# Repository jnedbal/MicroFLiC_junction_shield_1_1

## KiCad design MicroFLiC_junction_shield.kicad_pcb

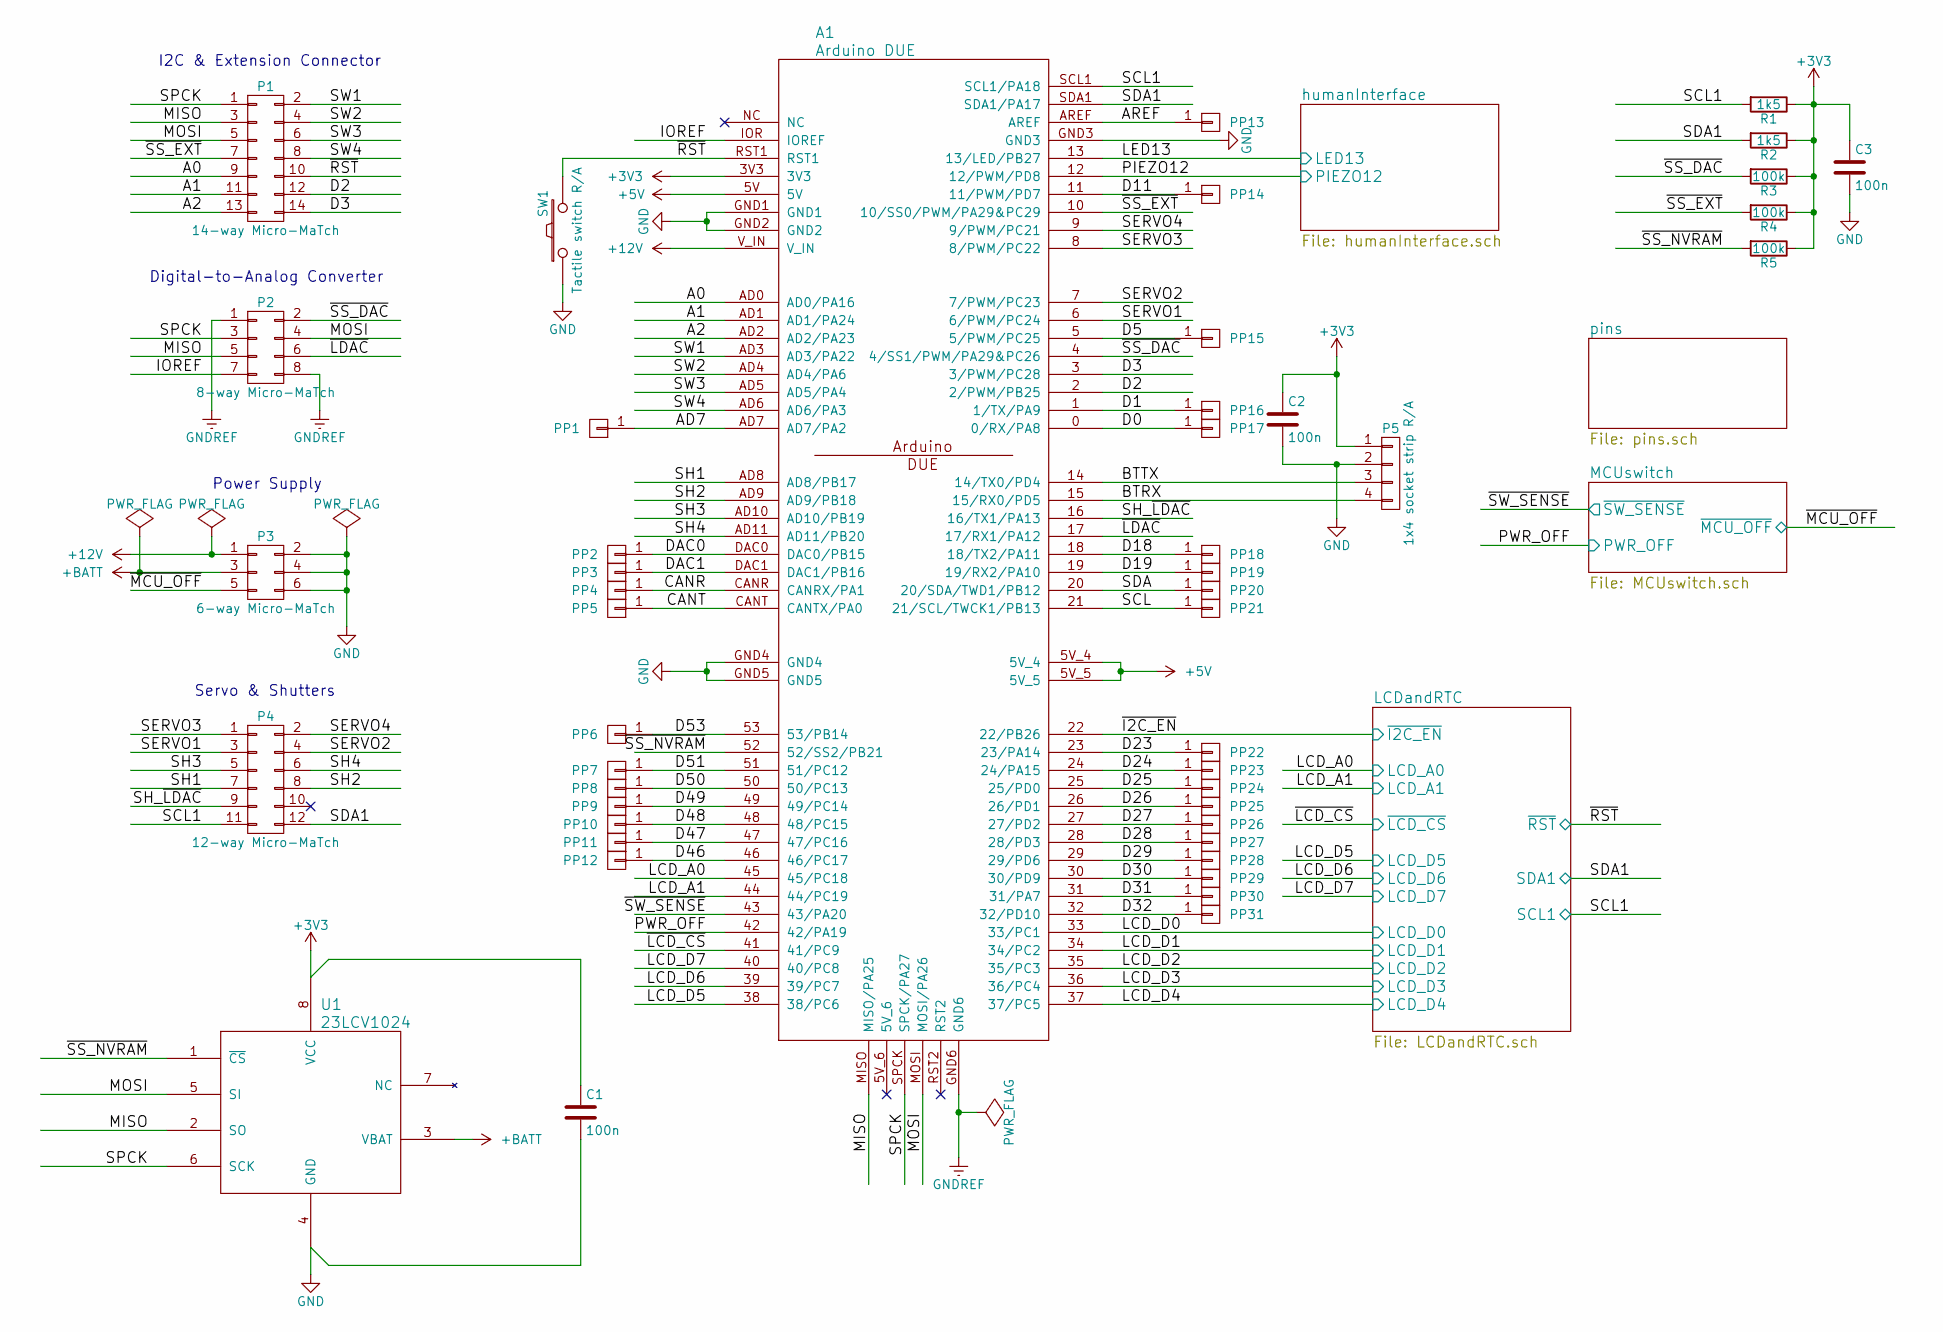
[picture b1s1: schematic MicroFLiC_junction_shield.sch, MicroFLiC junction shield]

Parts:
A1: Arduino DUE; ARDUINO_DUE; Part Number A000062
C1, C2, C3: 100n; C_0805; Part Number MC0805B104K250CT
P1: 14-way Micro-MaTch; 1-188275-4; Part Number 8-188275-4
P2: 8-way Micro-MaTch; 7-188275-8; Part Number 7-188275-8
P3: 6-way Micro-MaTch; 7-188275-6; Part Number 7-188275-6
P4: 12-way Micro-MaTch; 1-188275-2; Part Number 8-188275-2
P5: 1x4 socket strip R/A; Socket_Strip_Straight_1x04; Part Number SSW-104-02-G-S-RA
PP1, PP2, PP3, PP4, PP5, PP6, PP7, PP8, PP9, PP10, PP11, PP12, PP13, PP14, PP15, PP16, PP17, PP18, PP19, PP20, PP21, PP22, PP23, PP24, PP25, PP26, PP27, PP28, PP29, PP30, PP31: CONN_01X01; PIN_ARRAY_1
R1, R2: 1k5; R_0805; Part Number MCWR08X1501FTL
R3, R4, R5: 100k; R_0805; Part Number MCWR08X1003FTL
SW1: Tactile switch R/A; tactileSwitchRA; Part Number MCDTSA6-5N
U1: 23LCV1024; SOIC-8_3.9x4.9mm_Pitch1.27mm; Part Number 23LCV1024-I/SN

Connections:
+12V: A1.V_IN, P3.1; also elsewhere on the board
+BATT: P3.3, U1.3 (VBAT); also elsewhere on the board
/A0: A1.AD0 (AD0/PA16), P1.9
/A1: A1.AD1 (AD1/PA24), P1.11
/A2: A1.AD2 (AD2/PA23), P1.13
/AD7: A1.AD7 (AD7/PA2), PP1.1
/AREF: A1.AREF, PP13.1
/BTRX: A1.15 (15/RX0/PD5), P5.4
/BTTX: A1.14 (14/TX0/PD4), P5.3
/CANR: A1.CANR (CANRX/PA1), PP4.1
/CANT: A1.CANT (CANTX/PA0), PP5.1
/D0: A1.0 (0/RX/PA8), PP17.1
/D1: A1.1 (1/TX/PA9), PP16.1
/D2: A1.2 (2/PWM/PB25), P1.12
/D3: A1.3 (3/PWM/PC28), P1.14
/D5: A1.5 (5/PWM/PC25), PP15.1
/D11: A1.11 (11/PWM/PD7), PP14.1
/D18: A1.18 (18/TX2/PA11), PP18.1
/D19: A1.19 (19/RX2/PA10), PP19.1
/D23: A1.23 (23/PA14), PP22.1
/D24: A1.24 (24/PA15), PP23.1
/D25: A1.25 (25/PD0), PP24.1
/D26: A1.26 (26/PD1), PP25.1
/D27: A1.27 (27/PD2), PP26.1
/D28: A1.28 (28/PD3), PP27.1
/D29: A1.29 (29/PD6), PP28.1
/D30: A1.30 (30/PD9), PP29.1
/D46: A1.46 (46/PC17), PP12.1
/D47: A1.47 (47/PC16), PP11.1
/D48: A1.48 (48/PC15), PP10.1
/D49: A1.49 (49/PC14), PP9.1
/D50: A1.50 (50/PC13), PP8.1
/D51: A1.51 (51/PC12), PP7.1
/D53: A1.53 (53/PB14), PP6.1
/DAC0: A1.DAC0 (DAC0/PB15), PP2.1
/DAC1: A1.DAC1 (DAC1/PB16), PP3.1
/IOREF: A1.IOR (IOREF), P2.7
/LCDandRTC/LCD_A0: A1.45 (45/PC18); also elsewhere on the board
/LCDandRTC/LCD_A1: A1.44 (44/PC19); also elsewhere on the board
/LCDandRTC/LCD_D0: A1.33 (33/PC1); also elsewhere on the board
/LCDandRTC/LCD_D1: A1.34 (34/PC2); also elsewhere on the board
/LCDandRTC/LCD_D2: A1.35 (35/PC3); also elsewhere on the board
/LCDandRTC/LCD_D3: A1.36 (36/PC4); also elsewhere on the board
/LCDandRTC/LCD_D4: A1.37 (37/PC5); also elsewhere on the board
/LCDandRTC/LCD_D5: A1.38 (38/PC6); also elsewhere on the board
/LCDandRTC/LCD_D6: A1.39 (39/PC7); also elsewhere on the board
/LCDandRTC/LCD_D7: A1.40 (40/PC8); also elsewhere on the board
/LCDandRTC/SCL1: A1.SCL1 (SCL1/PA18), P4.11, R1.2; also elsewhere on the board
/LCDandRTC/SDA1: A1.SDA1 (SDA1/PA17), P4.12, R2.2; also elsewhere on the board
/LCDandRTC/~I2C_EN: A1.22 (22/PB26); also elsewhere on the board
/LCDandRTC/~LCD_CS: A1.41 (41/PC9); also elsewhere on the board
/LCDandRTC/~RST: A1.RST1, P1.10, SW1.2; also elsewhere on the board
/MCUswitch/PWR_OFF: A1.42 (42/PA19); also elsewhere on the board
/MCUswitch/~MCU_OFF: P3.5; also elsewhere on the board
/MCUswitch/~SW_SENSE: A1.43 (43/PA20); also elsewhere on the board
/MISO: A1.MISO (MISO/PA25), P1.3, P2.5, U1.2 (SO)
/MOSI: A1.MOSI (MOSI/PA26), P1.5, P2.4, U1.5 (SI)
/SCL: A1.21 (21/SCL/TWCK1/PB13), PP21.1
/SDA: A1.20 (20/SDA/TWD1/PB12), PP20.1
/SERVO1: A1.6 (6/PWM/PC24), P4.3
/SERVO2: A1.7 (7/PWM/PC23), P4.4
/SERVO3: A1.8 (8/PWM/PC22), P4.1
/SERVO4: A1.9 (9/PWM/PC21), P4.2
/SH1: A1.AD8 (AD8/PB17), P4.7
/SH2: A1.AD9 (AD9/PB18), P4.8
/SH3: A1.AD10 (AD10/PB19), P4.5
/SH4: A1.AD11 (AD11/PB20), P4.6
/SH_~LDAC: A1.16 (16/TX1/PA13), P4.9
/SPCK: A1.SPCK (SPCK/PA27), P1.1, P2.3, U1.6 (SCK)
/SW1: A1.AD3 (AD3/PA22), P1.2
/SW2: A1.AD4 (AD4/PA6), P1.4
/SW3: A1.AD5 (AD5/PA4), P1.6
/SW4: A1.AD6 (AD6/PA3), P1.8
/humanInterface/LED13: A1.13 (13/LED/PB27); also elsewhere on the board
/humanInterface/PIEZO12: A1.12 (12/PWM/PD8); also elsewhere on the board
/~LDAC: A1.17 (17/RX1/PA12), P2.6
/~SS_DAC: A1.4 (4/SS1/PWM/PA29&PC26), P2.2, R3.2
/~SS_EXT: A1.10 (10/SS0/PWM/PA29&PC29), P1.7, R4.2
/~SS_NVRAM: A1.52 (52/SS2/PB21), R5.2, U1.1 (~CS)
GNDREF: A1.GND6, P2.1, P2.8

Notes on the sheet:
I2C & Extension Connector
Digital-to-Analog Converter
Power Supply
Servo & Shutters

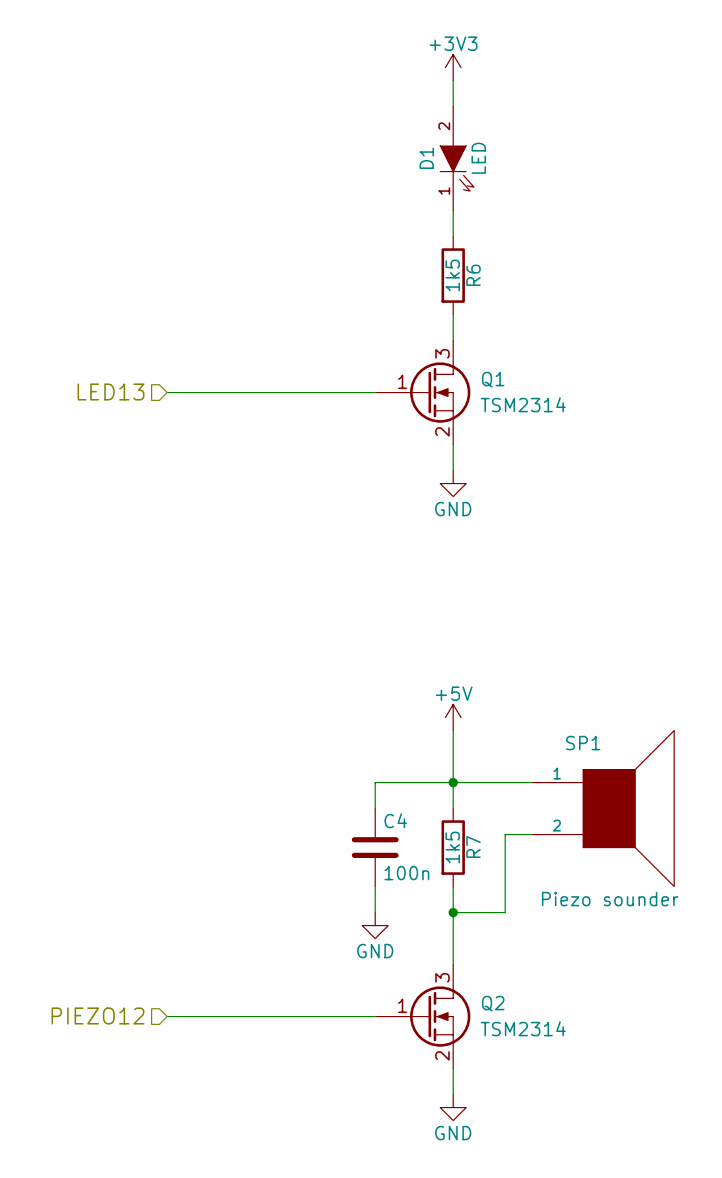
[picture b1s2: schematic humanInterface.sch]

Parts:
C4: 100n; C_0805; Part Number MC0805B104K250CT
D1: LED; LED-1206; Part Number HSMY-C150
Q1, Q2: TSM2314; SOT-23; Part Number TSM2314CX
R6, R7: 1k5; R_0805; Part Number MCWR08X1501FTL
SP1: Piezo sounder; piezo; Part Number PKM13EPYH4000-A0

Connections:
/humanInterface/LED13: Q1.1 (G); also elsewhere on the board
/humanInterface/PIEZO12: Q2.1 (G); also elsewhere on the board
unnamed: D1.1 (K), R6.1
unnamed: Q1.3 (D), R6.2
unnamed: Q2.3 (D), R7.2, SP1.2

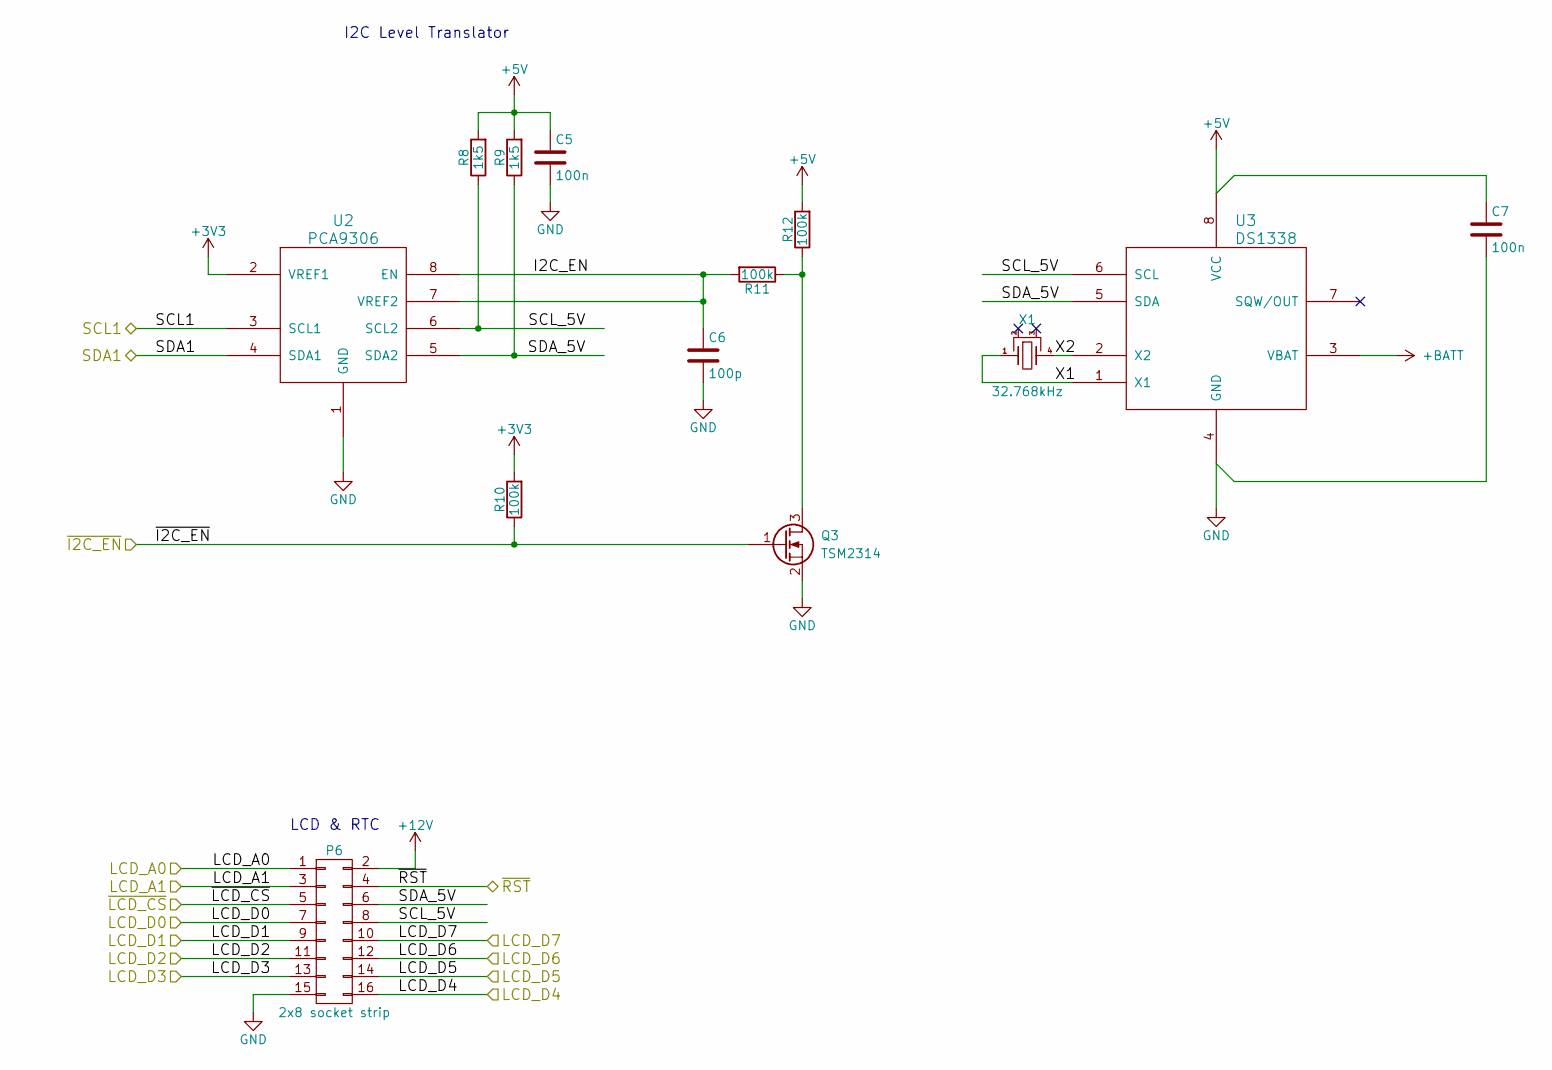
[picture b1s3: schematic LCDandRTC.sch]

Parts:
C5, C7: 100n; C_0805; Part Number MC0805B104K250CT
C6: 100p; C_0805; Part Number CGA4C2C0G2A101J060AA
P6: 2x8 socket strip; Socket_Strip_Straight_2x08; Part Number ESQ-108-33-G-D
Q3: TSM2314; SOT-23; Part Number TSM2314CX
R8, R9: 1k5; R_0805; Part Number MCWR08X1501FTL
R10, R11, R12: 100k; R_0805; Part Number MCWR08X1003FTL
U2: PCA9306; MSOP-8_3x3mm_Pitch0.65mm; Part Number PCA9306DP
U3: DS1338; SOIC-8_3.9x4.9mm_Pitch1.27mm; Part Number DS1338Z-33
X1: 32.768kHz; Crystal_8.7*3.7mm; Part Number FSRLF327

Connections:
+12V: P6.2; also elsewhere on the board
+BATT: U3.3 (VBAT); also elsewhere on the board
/LCDandRTC/I2C_EN: C6.1, R11.2, U2.7 (VREF2), U2.8 (EN)
/LCDandRTC/LCD_A0: P6.1; also elsewhere on the board
/LCDandRTC/LCD_A1: P6.3; also elsewhere on the board
/LCDandRTC/LCD_D0: P6.7; also elsewhere on the board
/LCDandRTC/LCD_D1: P6.9; also elsewhere on the board
/LCDandRTC/LCD_D2: P6.11; also elsewhere on the board
/LCDandRTC/LCD_D3: P6.13; also elsewhere on the board
/LCDandRTC/LCD_D4: P6.16; also elsewhere on the board
/LCDandRTC/LCD_D5: P6.14; also elsewhere on the board
/LCDandRTC/LCD_D6: P6.12; also elsewhere on the board
/LCDandRTC/LCD_D7: P6.10; also elsewhere on the board
/LCDandRTC/SCL1: U2.3 (SCL1); also elsewhere on the board
/LCDandRTC/SCL_5V: P6.8, R8.1, U2.6 (SCL2), U3.6 (SCL)
/LCDandRTC/SDA1: U2.4 (SDA1); also elsewhere on the board
/LCDandRTC/SDA_5V: P6.6, R9.1, U2.5 (SDA2), U3.5 (SDA)
/LCDandRTC/X1: U3.1 (X1), X1.1 (A)
/LCDandRTC/X2: U3.2 (X2), X1.4 (B)
/LCDandRTC/~I2C_EN: Q3.1 (G), R10.1; also elsewhere on the board
/LCDandRTC/~LCD_CS: P6.5; also elsewhere on the board
/LCDandRTC/~RST: P6.4; also elsewhere on the board
unnamed: Q3.3 (D), R11.1, R12.1

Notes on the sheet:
I2C Level Translator
LCD & RTC

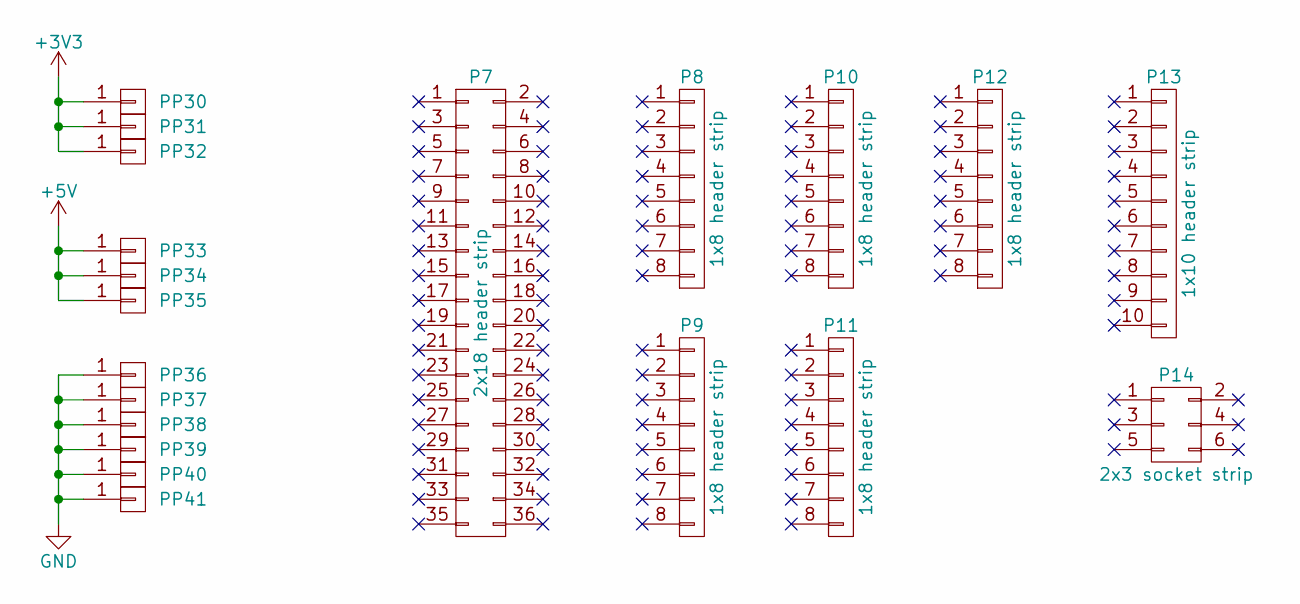
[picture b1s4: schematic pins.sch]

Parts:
P7: 2x18 header strip; Part Number 61303621121
P8, P9, P10, P11, P12: 1x8 header strip; Part Number M20-9990845
P13: 1x10 header strip; Part Number M20-9991046
P14: 2x3 socket strip; Part Number M20-7830346
PP30, PP31, PP32, PP33, PP34, PP35, PP36, PP37, PP38, PP39, PP40, PP41: CONN_01X01; PIN_ARRAY_1

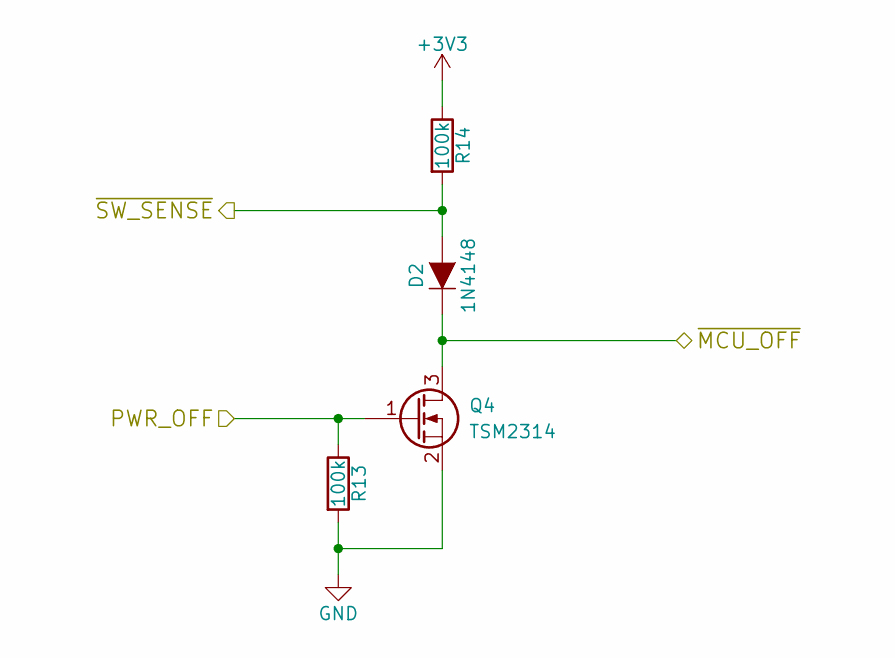
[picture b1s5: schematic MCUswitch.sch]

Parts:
D2: 1N4148; SOD-323; Part Number 1N4148WS
Q4: TSM2314; SOT-23; Part Number TSM2314CX
R13, R14: 100k; R_0805; Part Number MCWR08X1003FTL

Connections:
/MCUswitch/PWR_OFF: Q4.1 (G), R13.1; also elsewhere on the board
/MCUswitch/~MCU_OFF: D2.1 (K), Q4.3 (D); also elsewhere on the board
/MCUswitch/~SW_SENSE: D2.2 (A), R14.2; also elsewhere on the board

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
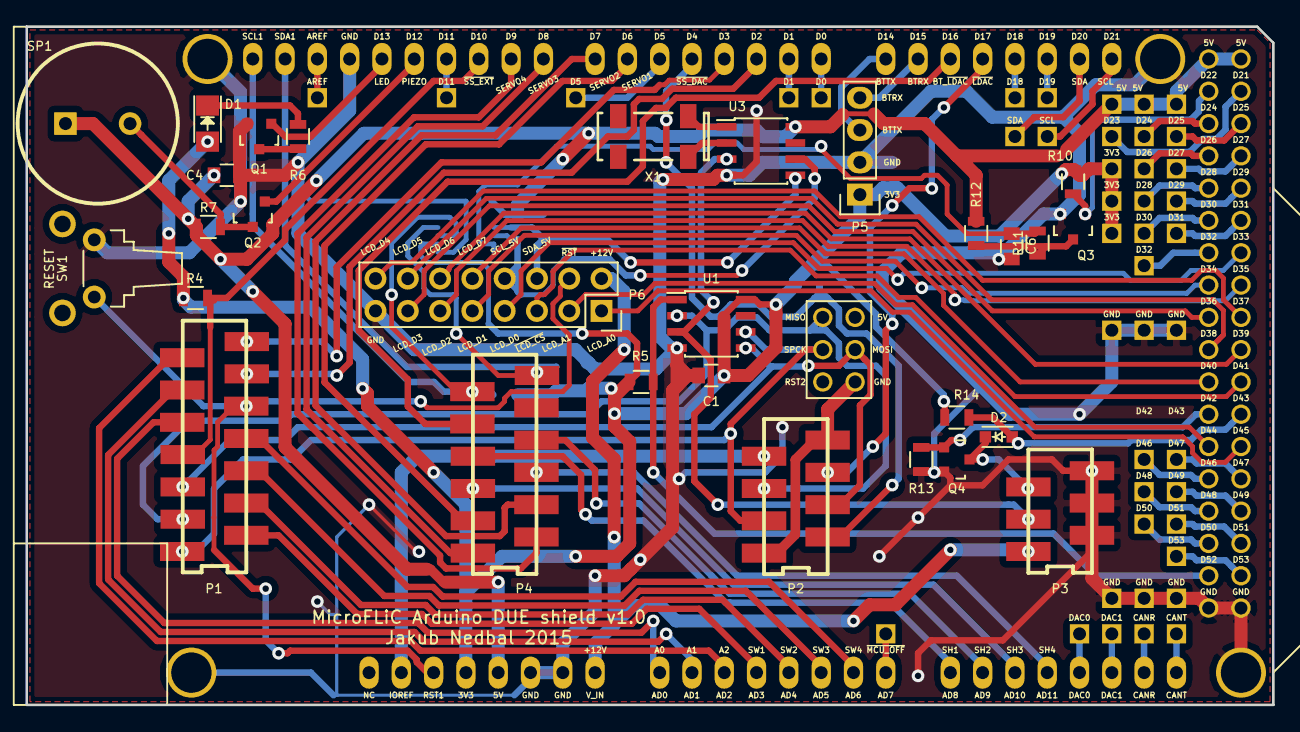
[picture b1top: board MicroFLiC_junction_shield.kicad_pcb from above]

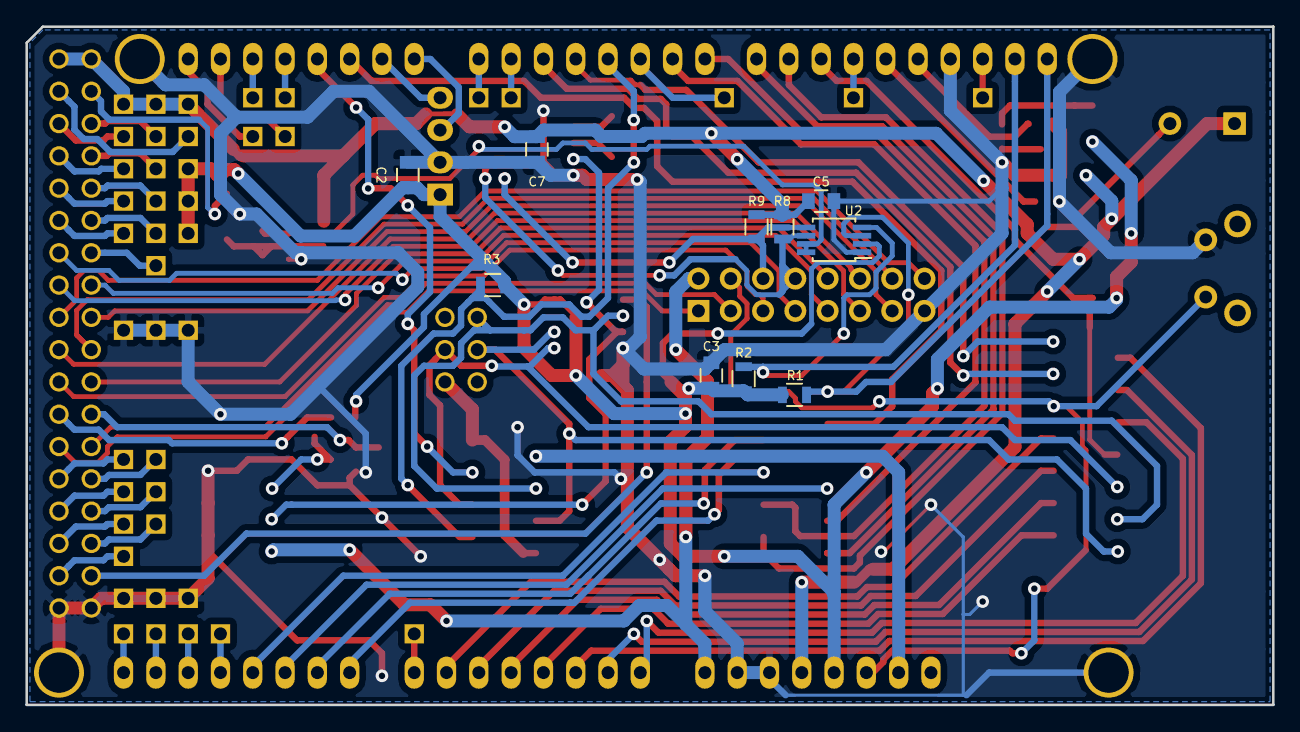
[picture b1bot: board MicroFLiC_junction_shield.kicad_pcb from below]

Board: 2 copper layers, 98.0 x 53.3 mm, 83 parts (10 on the bottom side), 94 nets.

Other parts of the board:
PP42, PP43: CONN_01X01; PIN_ARRAY_1

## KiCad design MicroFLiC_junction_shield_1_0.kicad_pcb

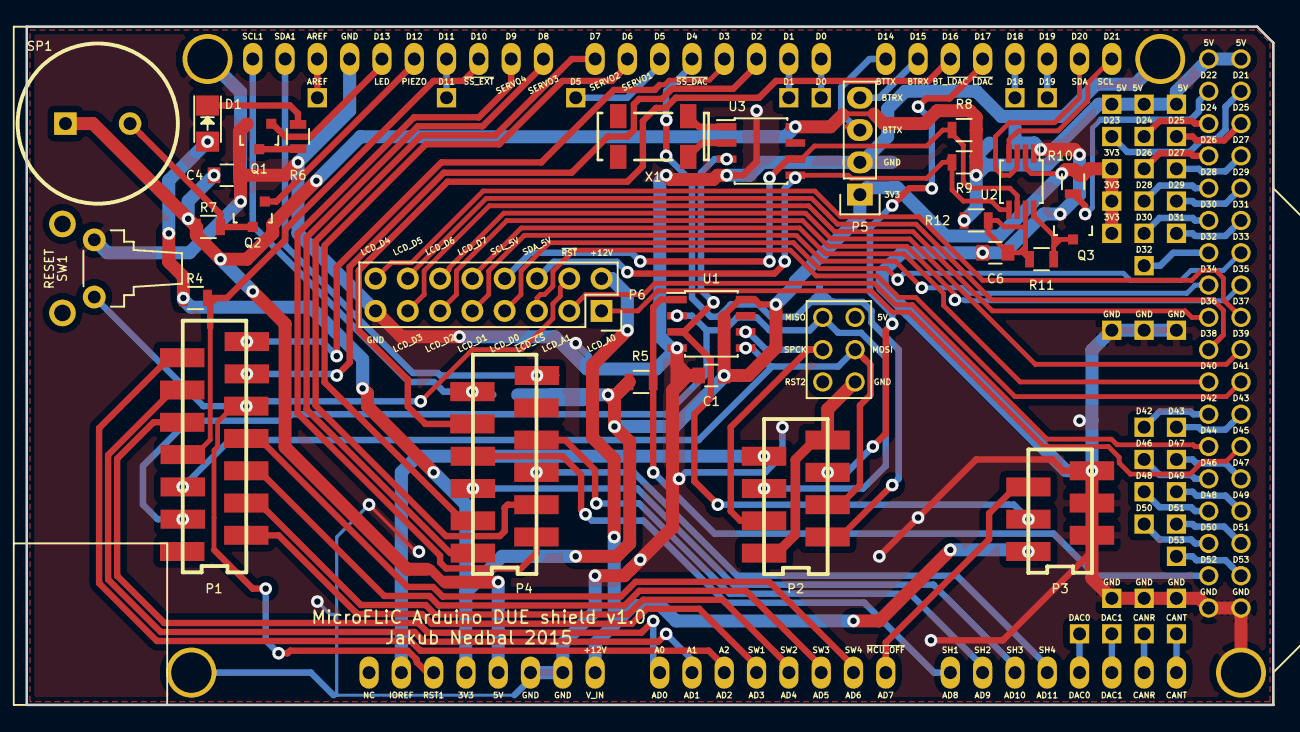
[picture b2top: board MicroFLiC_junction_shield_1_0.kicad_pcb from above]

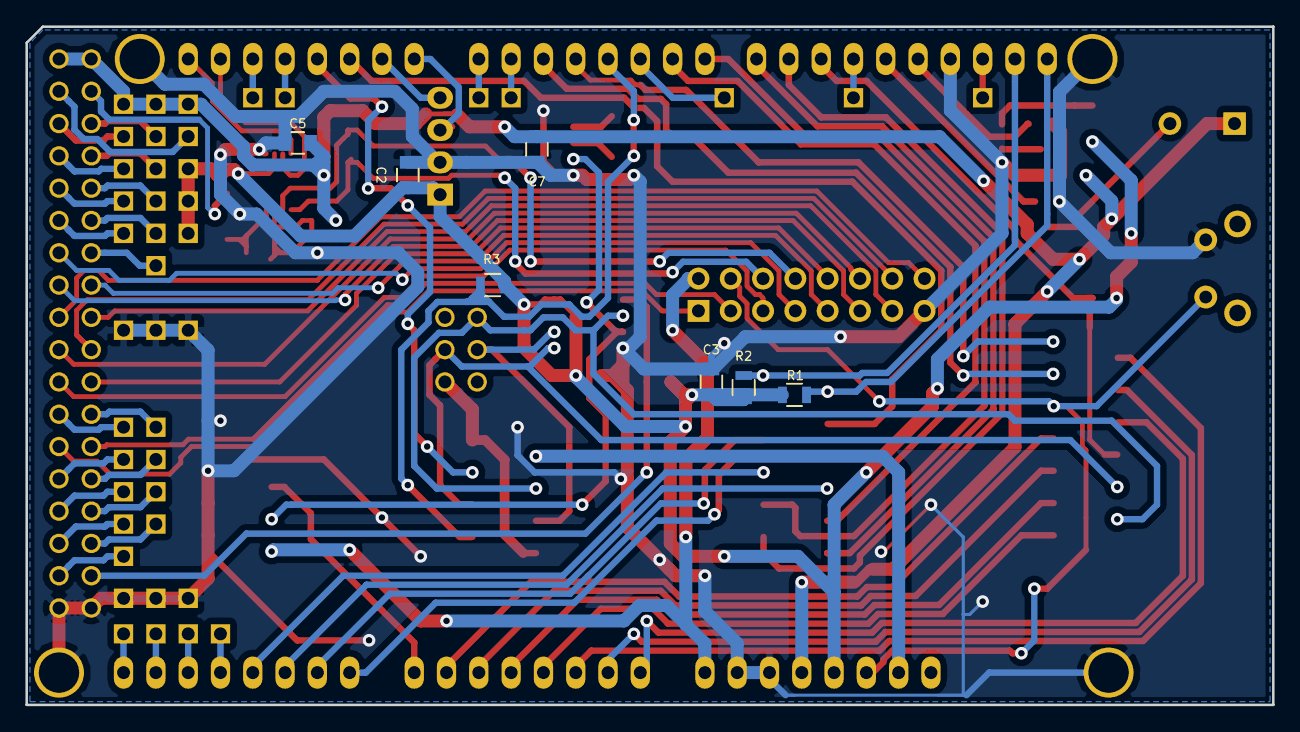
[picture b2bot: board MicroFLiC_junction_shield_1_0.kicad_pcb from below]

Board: 2 copper layers, 98.0 x 53.3 mm, 78 parts (7 on the bottom side), 93 nets.

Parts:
C1, C2, C3, C4, C5, C6, C7: 100n; C_0805
D1: LED; LED-1206
P1: CONN_02X07; 1-188275-4
P2: CONN_02X04; 7-188275-8
P3: CONN_02X03; 7-188275-6
P4: CONN_02X06; 1-188275-2
P5: CONN_01X04; Socket_Strip_Straight_1x04
P6: CONN_02X08; Socket_Strip_Straight_2x08
PP1, PP2, PP3, PP4, PP5, PP6, PP7, PP8, PP9, PP10, PP11, PP12, PP13, PP14, PP15, PP16, PP17, PP18, PP19, PP20, PP21, PP22, PP23, PP24, PP25, PP26, PP27, PP28, PP29, PP30, PP31, PP32, PP33, PP34, PP35, PP36, PP37, PP38, PP39, PP40, PP41, PP42: CONN_01X01; PIN_ARRAY_1
Q1, Q2, Q3: TSM2314; SOT-23
R1, R2, R6, R7, R8, R9, R12: 1k5; R_0805
R3, R4, R5, R10: 47k; R_0805
R11: 180k; R_0805
SHIELD1: ARDUINO_DUE_SHIELD; ARDUINO_DUE
SP1: PIEZO SOUNDER; piezo
SW1: SW_PUSH; tactileSwitchRA
U1: 23LVC1024; SOIC-8_3.9x4.9mm_Pitch1.27mm
U2: PCA9306; MSOP-8_3x3mm_Pitch0.65mm
U3: DS1338; SOIC-8_3.9x4.9mm_Pitch1.27mm
X1: 32.768kHz; Crystal_8.7*3.7mm

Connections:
+3V3: C1.1, C2.1, C3.1, D1.2, P5.1, PP31.1, PP32.1, PP33.1, R1.1, R2.1, R3.1, R4.1, R5.1, R10.2, SHIELD1.3V3, U1.8, U2.2
+5V: C4.1, C5.1, C7.1, PP34.1, PP35.1, PP36.1, R7.1, R8.2, R9.2, R12.2, SHIELD1.5V, SHIELD1.5V_4, SHIELD1.5V_5, SP1.1, U3.8
+12V: P3.1, P6.2, SHIELD1.V_IN
+BATT: P3.3, U1.3, U3.3
/A0: P1.9, SHIELD1.AD0
/A1: P1.11, SHIELD1.AD1
/A2: P1.13, SHIELD1.AD2
/AREF: PP14.1, SHIELD1.AREF
/BTRX: P5.4, SHIELD1.15
/BTTX: P5.3, SHIELD1.14
/CANR: PP3.1, SHIELD1.CANR
/CANT: PP4.1, SHIELD1.CANT
/D0: PP18.1, SHIELD1.0
/D1: PP17.1, SHIELD1.1
/D2: P1.12, SHIELD1.2
/D3: P1.14, SHIELD1.3
/D5: PP16.1, SHIELD1.5
/D11: PP15.1, SHIELD1.11
/D18: PP19.1, SHIELD1.18
/D19: PP20.1, SHIELD1.19
/D23: PP21.1, SHIELD1.23
/D24: PP22.1, SHIELD1.24
/D25: PP23.1, SHIELD1.25
/D26: PP24.1, SHIELD1.26
/D27: PP25.1, SHIELD1.27
/D28: PP26.1, SHIELD1.28
/D29: PP27.1, SHIELD1.29
/D30: PP28.1, SHIELD1.30
/D31: PP29.1, SHIELD1.31
/D32: PP30.1, SHIELD1.32
/D42: PP13.1, SHIELD1.42
/D43: PP12.1, SHIELD1.43
/D46: PP11.1, SHIELD1.46
/D47: PP10.1, SHIELD1.47
/D48: PP9.1, SHIELD1.48
/D49: PP8.1, SHIELD1.49
/D50: PP7.1, SHIELD1.50
/D51: PP6.1, SHIELD1.51
/D53: PP5.1, SHIELD1.53
/DAC0: PP1.1, SHIELD1.DAC0
/DAC1: PP2.1, SHIELD1.DAC1
/IOREF: P2.7, SHIELD1.IOR
/LCDandRTC/LCD_A0: P6.1, SHIELD1.45
/LCDandRTC/LCD_A1: P6.3, SHIELD1.44
/LCDandRTC/LCD_D0: P6.7, SHIELD1.33
/LCDandRTC/LCD_D1: P6.9, SHIELD1.34
/LCDandRTC/LCD_D2: P6.11, SHIELD1.35
/LCDandRTC/LCD_D3: P6.13, SHIELD1.36
/LCDandRTC/LCD_D4: P6.16, SHIELD1.37
/LCDandRTC/LCD_D5: P6.14, SHIELD1.38
/LCDandRTC/LCD_D6: P6.12, SHIELD1.39
/LCDandRTC/LCD_D7: P6.10, SHIELD1.40
/LCDandRTC/SCL: SHIELD1.21, U2.4
/LCDandRTC/SCL_5V: P6.8, R8.1, U2.6, U3.6
/LCDandRTC/SDA: SHIELD1.20, U2.3
/LCDandRTC/SDA_5V: P6.6, R9.1, U2.5, U3.5
/LCDandRTC/X1: U3.1, X1.1
/LCDandRTC/X2: U3.2, X1.4
/LCDandRTC/~I2C_EN: Q3.1, R10.1, SHIELD1.22
/LCDandRTC/~LCD_CS: P6.5, SHIELD1.41
/LCDandRTC/~RST: P1.10, P6.4, SHIELD1.RST1, SW1.2
/MISO: P1.3, P2.5, SHIELD1.MISO, U1.2
/MOSI: P1.5, P2.4, SHIELD1.MOSI, U1.5
/SCL1: P4.11, R1.2, SHIELD1.SCL1
/SDA1: P4.12, R2.2, SHIELD1.SDA1
/SERVO1: P4.3, SHIELD1.6
/SERVO2: P4.4, SHIELD1.7
/SERVO3: P4.1, SHIELD1.8
/SERVO4: P4.2, SHIELD1.9
/SH1: P4.7, SHIELD1.AD8
/SH2: P4.8, SHIELD1.AD9
/SH3: P4.5, SHIELD1.AD10
/SH4: P4.6, SHIELD1.AD11
/SH_~LDAC: P4.9, SHIELD1.16
/SPCK: P2.3, SHIELD1.SPCK, U1.6
/SW1: P1.2, SHIELD1.AD3
/SW2: P1.4, SHIELD1.AD4
/SW3: P1.6, SHIELD1.AD5
/SW4: P1.8, SHIELD1.AD6
/humanInterface/LED13: Q1.1, SHIELD1.13
/humanInterface/PIEZO12: Q2.1, SHIELD1.12
/~LDAC: P2.6, SHIELD1.17
/~MCU_OFF: P3.5, SHIELD1.AD7
/~SS_DAC: P2.2, R3.2, SHIELD1.4
/~SS_EXT: P1.7, R4.2, SHIELD1.10
/~SS_NVRAM: R5.2, SHIELD1.52, U1.1
GND: C1.2, C2.2, C3.2, C4.2, C5.2, C6.2, C7.2, P3.2, P3.4, P3.6, P5.2, P6.15, PP37.1, PP38.1, PP39.1, PP40.1, PP41.1, PP42.1, Q1.2, Q2.2, Q3.2, SHIELD1.GND1, SHIELD1.GND2, SHIELD1.GND3, SHIELD1.GND4, SHIELD1.GND5, SW1.1, U1.4, U2.1, U3.4
GNDREF: P2.1, P2.8, SHIELD1.GND6
unnamed: C6.1, R11.1, R12.1, U2.7
unnamed: D1.1, R6.1
unnamed: Q1.3, R6.2
unnamed: Q2.3, R7.2, SP1.2
unnamed: Q3.3, R11.2, U2.8

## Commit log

2016-01-06 First commit and final production board v1.0
2016-02-14 Last commit in v1.0
2016-02-14 First commit of version 1.1
2016-02-15 Started fully describing components
2016-02-24 Added MCU power control (MCUswitch.sch)
2016-02-25 Updated PCB for MCU switch, fixed SPCK connection, added correct angled connector for BT
2016-02-25 Finished adding full part descriptions
2016-02-29 Changed 3D drawing to include ESQ connector for LCD
2016-03-02 Changed part number or yellow LED
2016-03-02 Incorporated un-pulled changes
2016-03-18 Changed SHIELD1 to A1, changed SOD-323 footprint for easier soldering
2016-03-18 Changed layout of I2C buffer enabling
2016-07-06 Fixed crossed-over SCL and SDA lines
2016-07-07 Changed LCD shield from Wire to Wire1
2016-07-07 Tidied up few routes
